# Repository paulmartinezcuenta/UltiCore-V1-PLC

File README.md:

# UltiCore V1 - ESP32-Based Industrial PLC 

UltiCore V1 is a high-reliability, industrial-grade Programmable Logic Controller (PLC) custom-designed around the **ESP32-WROOM-32D** architecture. Engineered for harsh electrical environments, this board features high-density optical isolation, dedicated buffered data buses, and a robust power management system.

---

##  Advanced Hardware Architecture & Engineering

### 1. Dual-Bus Data Architecture & Control Logic
* **Buffered Bus Isolation:** Implements octal three-state buffers (**74HC541TS**) to split control signals into dedicated **Power Data Buses** and **Analog Data Buses**. This topology isolates the MCU pins, maximizes fan-out capability, and prevents EMI crosstalk from high-current switching sections.
* **Industrial Output Stage (8-Channel Relay Matrix):** Features 8 independent mechanical relays driven by robust **2N3904** BJT switching circuits. Each channel is equipped with hardwired pull-down networks for deterministic power-up states and **RR1VWM6STFTR** flyback suppression diodes to clamp inductive back-EMF spikes.

### 2. High-Density Input Conditioning & Galvanic Isolation
* **Optically Isolated Digital Inputs:** 8 industrial-level input channels (`IN0`-`IN7`) isolated via high-density **ILD207T** dual optocouplers, establishing complete galvanic separation between the 24V field domain and the 3.3V logic domain.
* **Hardware Debouncing & Waveshaping:** Optocoupler outputs are routed through **74HC14** Hex Schmitt-Trigger inverters to suppress mechanical switch bounce and electrical noise, delivering sharp, clean square waves to the MCU.

### 3. Industrial Power Supply & Protection Framework
* **High-Efficiency Buck Topology:** Integrates an **LM2576HVS-3.3** switching regulator paired with a **100µH** power inductor and a **B330A** Schottky diode to efficiently step down standard industrial 24VDC rails directly to a stable 3.3V rail.
* **Smart Dual-Power Protection (Anti-USB & 24V Cross-Protection):** Utilizes an **LM358DR** operational amplifier comparator circuit coupled with a **PC817** optocoupler and an **FQD11P06** P-Channel MOSFET. This layout actively prevents reverse-current backfeeding and hardware damage when both the high-voltage field power and USB-C programming interface are active simultaneously.
* **Front-End Overcurrent & Polarity Defense:** Equipped with a standard 5x20mm cartridge fuse assembly and a high-current **5S14** blocking diode for reverse-polarity protection.

### 4. Modern Interface & ESD Compliance
* **USB-C Interface:** Modern USB-C implementation driven by a **CH340C** USB-to-UART bridge with an integrated dual-transistor auto-reset/boot-loader circuit.
* **Transient Voltage Suppression:** High-speed **LESD5D5.0CT1G** TVS diode arrays deployed on critical USB data lines (`D+`/`D-`) for localized ESD clamping.

---

## Repository Structure

```text
├── Hardware/        # KiCad schematic captures, multi-layer layout files, and structural BOM
├── Firmware/        # Modular C/C++ source code and RTOS industrial automation tasks
└── Docs/            # Hardware layout sheets, pinout mapping, and component datasheets

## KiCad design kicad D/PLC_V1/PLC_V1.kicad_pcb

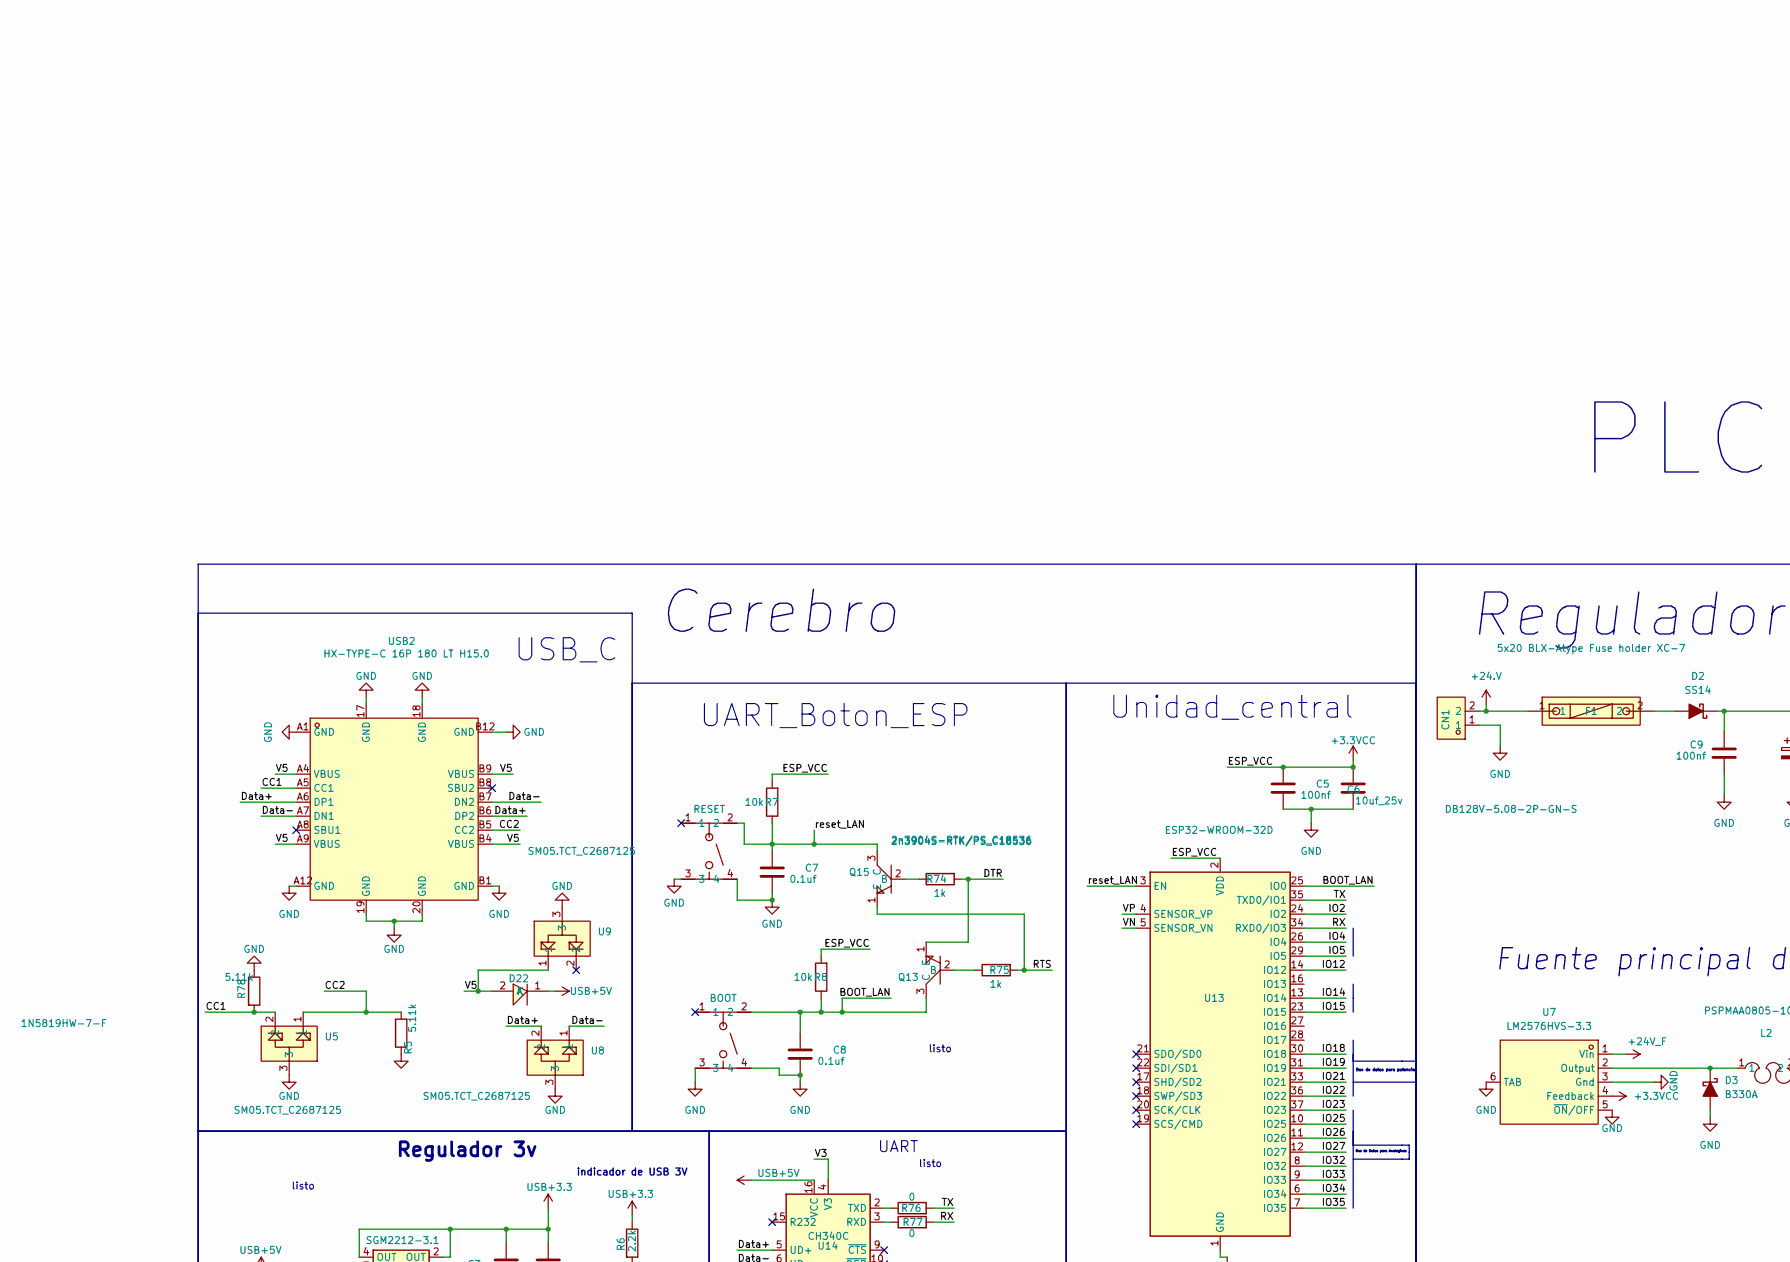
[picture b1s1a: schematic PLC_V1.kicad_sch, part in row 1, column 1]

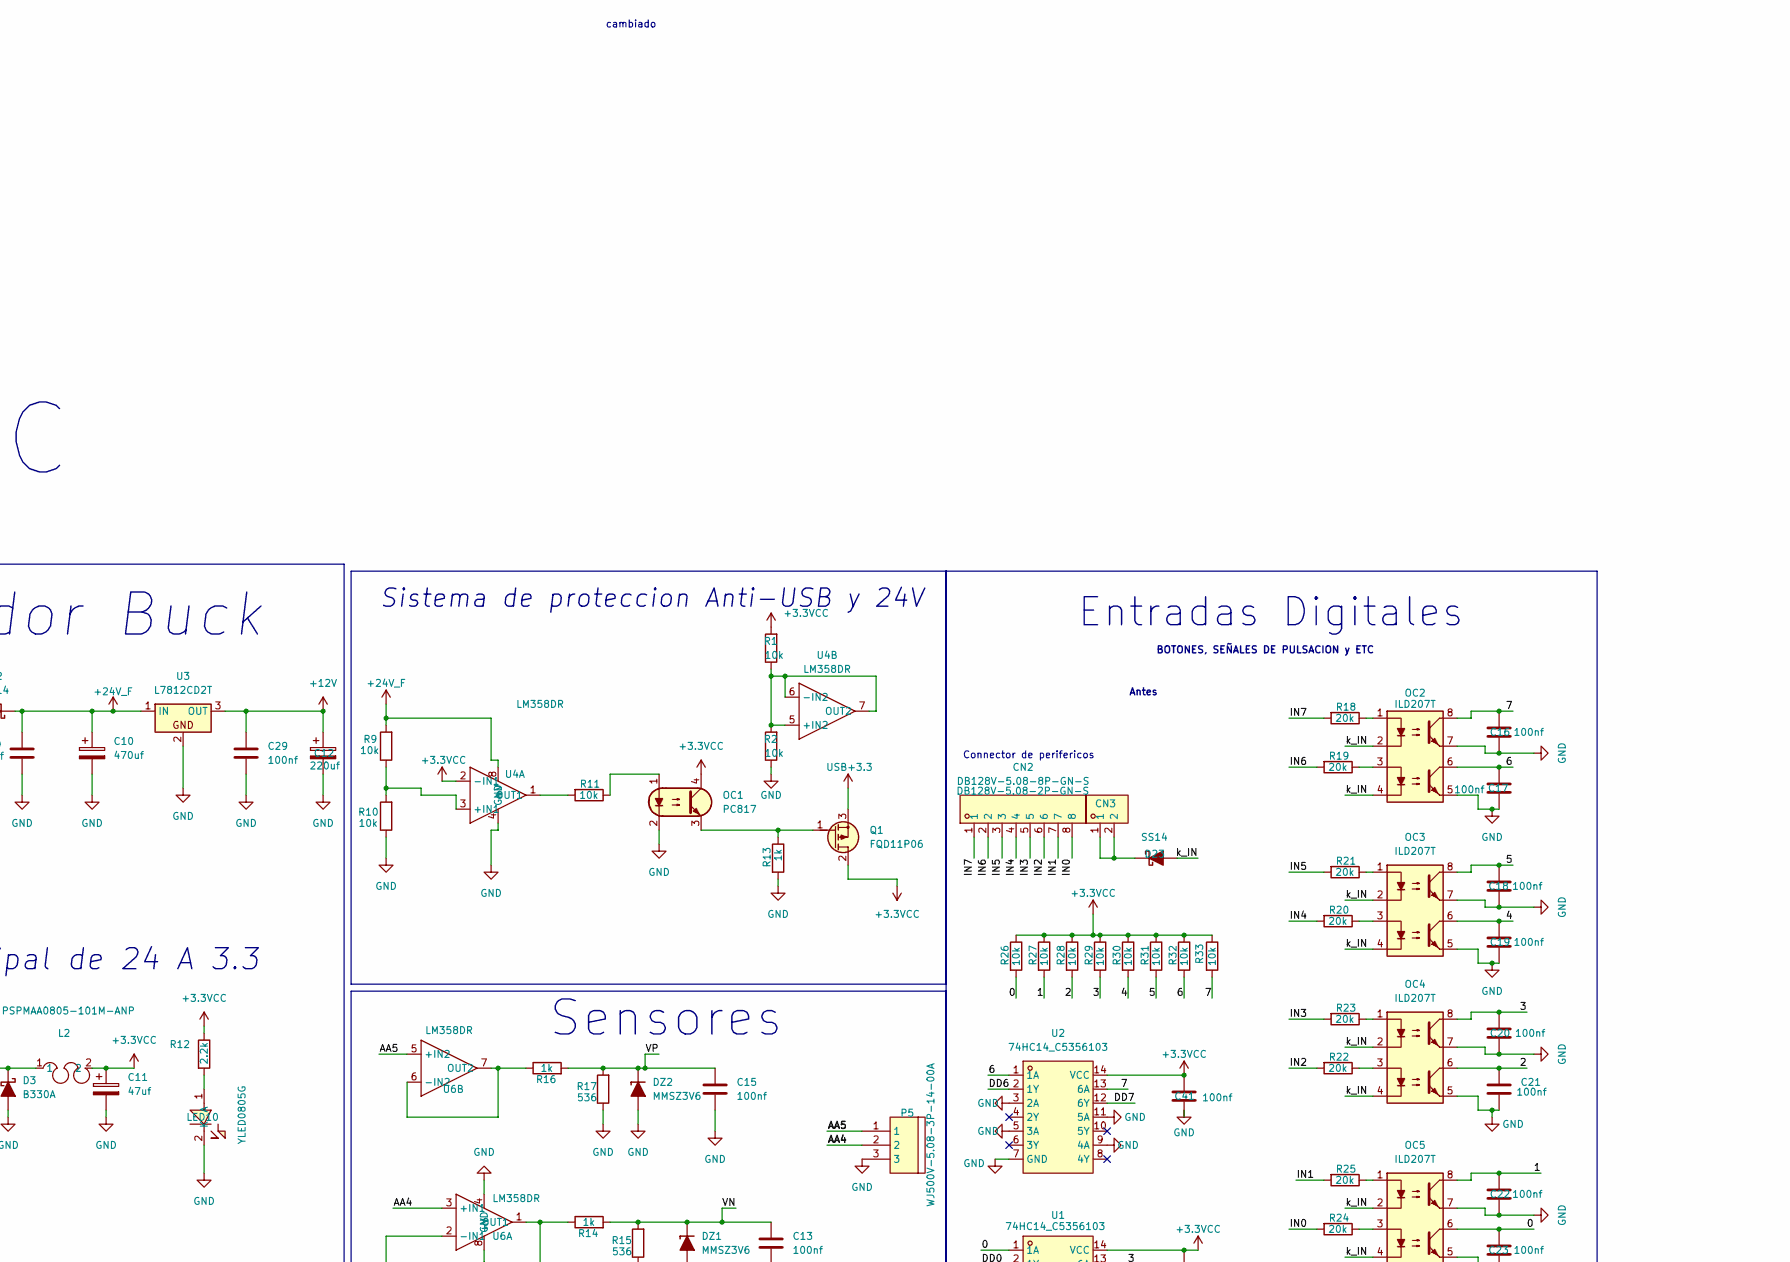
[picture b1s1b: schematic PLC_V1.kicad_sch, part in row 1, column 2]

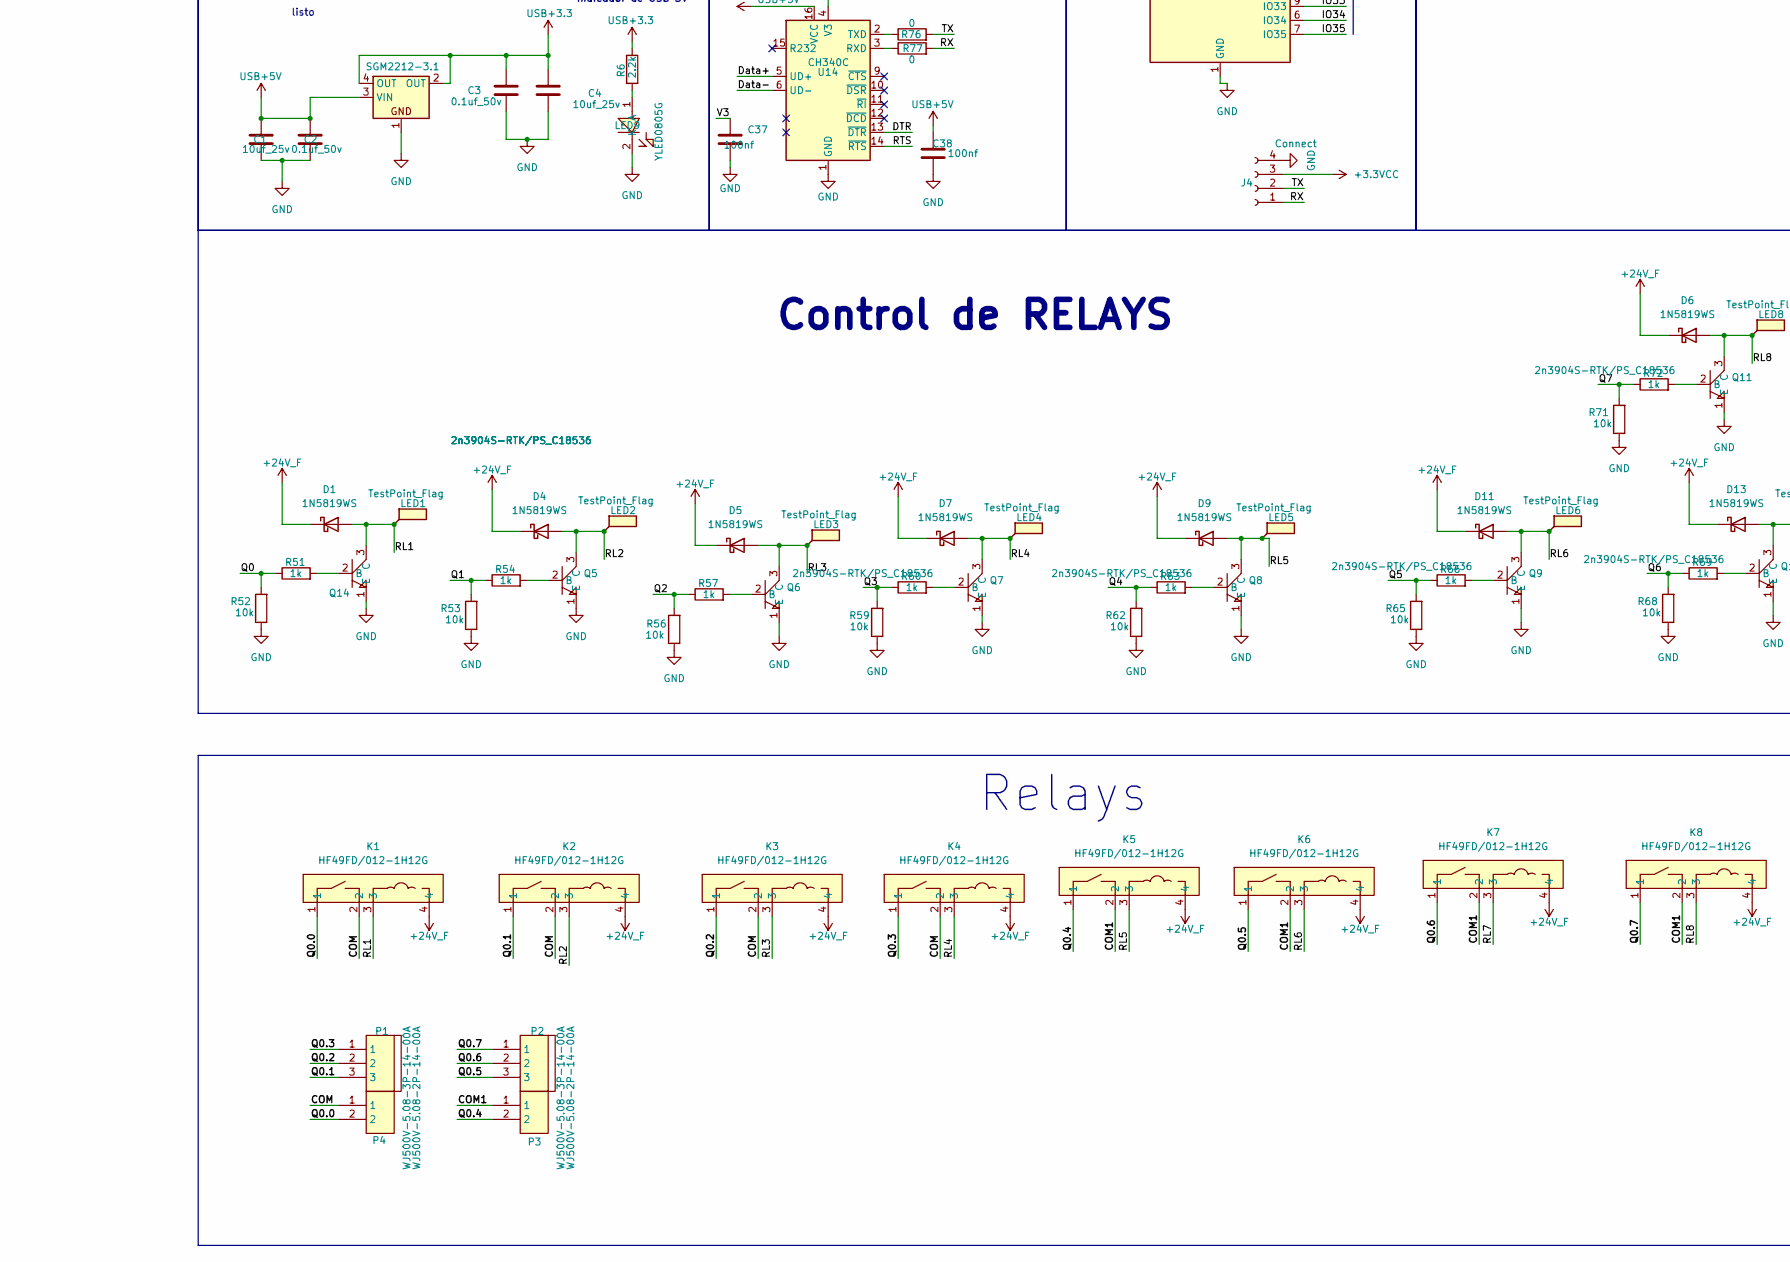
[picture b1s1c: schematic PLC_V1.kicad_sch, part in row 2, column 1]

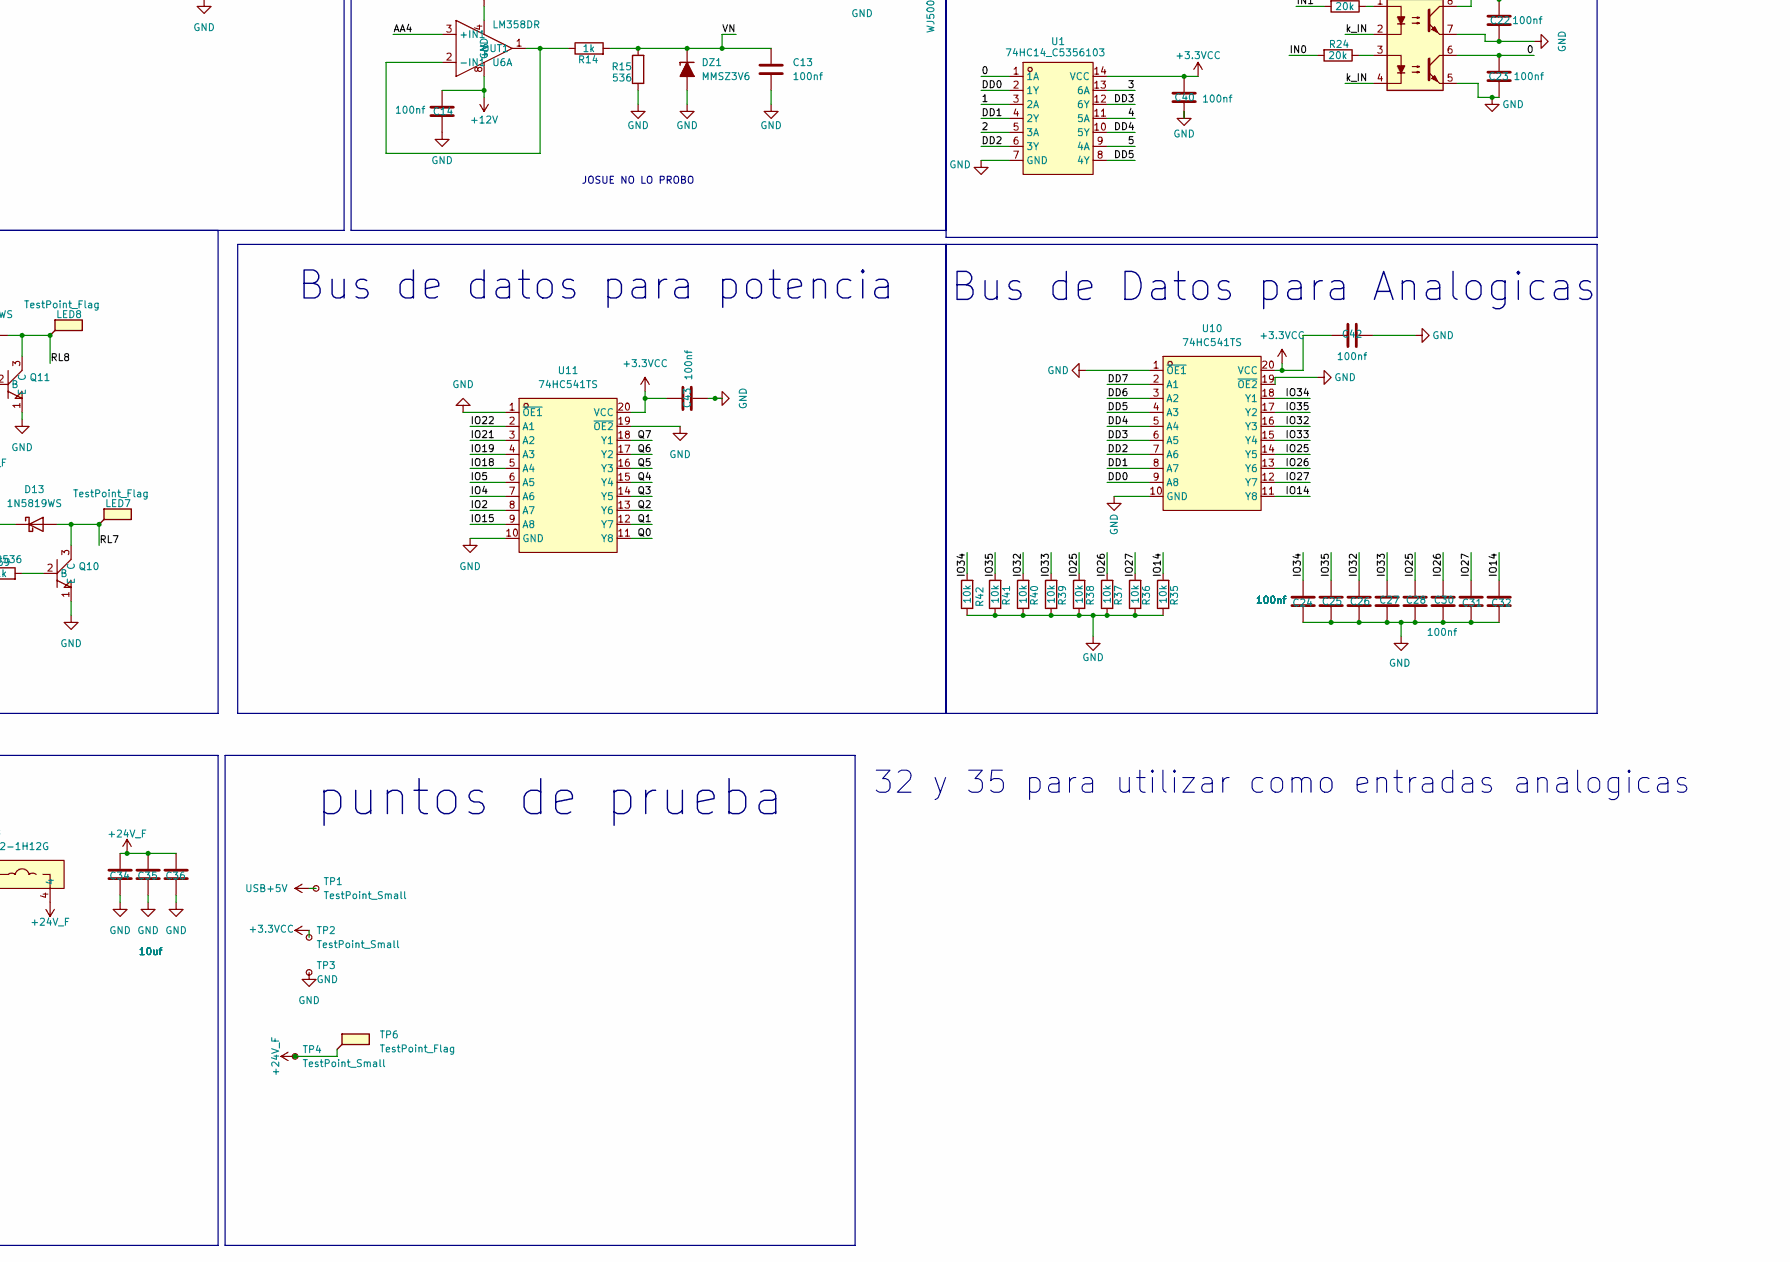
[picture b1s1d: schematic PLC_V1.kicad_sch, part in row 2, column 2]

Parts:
C1, C4, C6: 10uf_25v; C_0805_2012Metric_Pad1.18x1.45mm_HandSolder
C2, C3: 0.1uf_50v; C_0805_2012Metric_Pad1.18x1.45mm_HandSolder
C5, C9, C13, C14, C15, C16, C17, C18, C19, C20, C21, C22, C23, C24, C25, C26, C27, C28, C29, C30, C31, C32, C37, C38, C40, C41, C42, C43: 100nf; C_0805_2012Metric_Pad1.18x1.45mm_HandSolder
C7, C8: 0.1uf; C_0805_2012Metric_Pad1.18x1.45mm_HandSolder
C10: 470uf; C_Elec_10x10.2; LCSC C72518
C11: 47uf; C_Elec_6.3x7.7; LCSC C72523
C12: 220uf; C_Elec_8x10.2
C34, C35, C36: 10uf; C_0805_2012Metric_Pad1.18x1.45mm_HandSolder
CN1, CN3: DB128V-5.08-2P-GN-S; CONN-TH_2P-P5.08_DIBO_DB128V-5.08; LCSC Part C2915639
CN2: DB128V-5.08-8P-GN-S; CONN-TH_8P-P5.08_DB128V-5.08-8P-GN-S; LCSC Part C5143711
D1, D4, D5, D6, D7, D9, D11, D13: 1N5819WS; D_SOD-323
D2, D23: SS14; D_SMA
D3: B330A; D_SMA
D22: 1N5819HW-7-F; SOD-123_L2.7-W1.6-LS3.7-RD; LCSC Part C82544
DZ1, DZ2: MMSZ3V6; D_SOD-123
F1: 5x20 BLX-Atype Fuse holder XC-7; FUSE-TH_L22.6-W9.0; LCSC Part C3131
J4: Connect; PinHeader_1x04_P2.00mm_Vertical
K1, K2, K3, K4, K5, K6, K7, K8: HF49FD/012-1H12G; RELAY-TH_HF49FD-012-1H12G; LCSC Part C340662
L2: PSPMAA0805-101M-ANP; IND-SMD_L8.5-W8.0_PCC-M0854M; LCSC Part C2962892
LED1, LED2, LED3, LED4, LED5, LED6, LED7, LED8: TestPoint_Flag; SolderWirePad_1x01_SMD_1x2mm
LED9, LED10: YLED0805G; LED0805-FD-GREEN; LCSC Part C25170728
OC1: PC817; DIP-4_W7.62mm_SMDSocket_SmallPads
OC2, OC3, OC4, OC5: ILD207T; SO-8_3.9x6.2mm_P1.27mm
P1, P2, P5: WJ500V-5.08-3P-14-00A; CONN-TH_3P-P5.00_WJ500V-5.08-3P; LCSC Part C72334
P3, P4: WJ500V-5.08-2P-14-00A; CONN-TH_2P-P5.00_WJ500V-5.08-2P; LCSC Part C8465
Q1: FQD11P06; TO-252-2
Q5, Q6, Q7, Q8, Q9, Q10, Q11, Q13, Q14, Q15: 2n3904S-RTK/PS_C18536; SOT-23-3_L2.9-W1.3-P1.90-LS2.4-TR; LCSC Part C18536
R1, R2, R7, R8, R9, R10, R11, R26, R27, R28, R29, R30, R31, R32, R33, R35, R36, R37, R38, R39, R40, R41, R42, R52, R53, R56, R59, R62, R65, R68, R71: 10k; R_0805_2012Metric_Pad1.20x1.40mm_HandSolder
R5, R78: 5.11k; R_0805_2012Metric_Pad1.20x1.40mm_HandSolder
R6, R12: 2.2k; R_0805_2012Metric_Pad1.20x1.40mm_HandSolder
R13, R14, R16, R51, R54, R57, R60, R63, R66, R69, R72, R74, R75: 1k; R_0805_2012Metric_Pad1.20x1.40mm_HandSolder
R15, R17: 536; R_0805_2012Metric_Pad1.20x1.40mm_HandSolder
R18, R19, R20, R21, R22, R23, R24, R25: 20k; R_0805_2012Metric_Pad1.20x1.40mm_HandSolder
R76, R77: 0; R_0805_2012Metric_Pad1.20x1.40mm_HandSolder
SGM2212-3.1: SOT-223
SW1: BOOT; SW-SMD_4P-L6.0-W6.0-P4.50-LS8.2; LCSC Part C7528752
SW3: RESET; SW-SMD_4P-L6.0-W6.0-P4.50-LS8.2; LCSC Part C7528752
TP1, TP2, TP4: TestPoint_Small; TestPoint_Pad_2.0x2.0mm
TP3: GND; TestPoint_Pad_2.0x2.0mm
TP6: TestPoint_Flag; SolderWirePad_1x01_SMD_1.5x3mm
U1, U2: 74HC14_C5356103; SOIC-14_L8.7-W3.9-P1.27-LS6.0-BL; LCSC Part C5356103
U3: L7812CD2T; TO-263-2
U4, U6: LM358DR; SOIC-8_L5.0-W4.0-P1.27-LS6.0-BL; LCSC Part C5423
U5, U8, U9: SM05.TCT_C2687125; SOT-23-3_L2.9-W1.3-P1.90-LS2.4; LCSC Part C2687125
U7: LM2576HVS-3.3; PG-TO-263-5_L10.2-W8.7-P1.70-LS14.4-BR; LCSC Part C347436
U10, U11: 74HC541TS; TSSOP-20_L6.5-W4.4-P0.65-LS6.4-BL; LCSC Part C41433435
U13: ESP32-WROOM-32D
U14: CH340C; SOIC-16_3.9x9.9mm_P1.27mm
USB2: HX-TYPE-C 16P 180 LT H15.0; USB-C-SMD_HX-TYPE-C-16P-180-LT-H15.0; LCSC Part C49261573

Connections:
+3.3VCC: C5.1, C6.1, C11.1, C40.2, C41.2, C42.1, C43.2, J4.3, L2.2, OC1.4, Q1.2 (D), R1.2, R7.2, R8.2, R12.1, R26.1, R27.1, R28.1, R29.1, R30.1, R31.1, R32.1, R33.1, TP2.1, U1.14 (VCC), U2.14 (VCC), U4.2 (-IN1), U7.4 (Feedback), U10.20 (VCC), U11.20 (VCC), U13.2 (VDD)
+12V: C12.1, C14.1, C29.1, U3.3 (OUT), U6.8 (+V)
+24.V: CN1.2, F1.1
+24V_F: C9.1, C10.1, C34.1, C35.1, C36.1, D1.1 (K), D2.1 (K), D4.1 (K), D5.1 (K), D6.1 (K), D7.1 (K), D9.1 (K), D11.1 (K), D13.1 (K), K1.4, K2.4, K3.4, K4.4, K5.4, K6.4, K7.4, K8.4, R9.2, TP4.1, TP6.1, U3.1 (IN), U4.8 (+V), U7.1 (Vin)
/0: C23.1, OC5.6, R26.2, U1.1 (1A)
/1: C22.1, OC5.8, R27.2, U1.3 (2A)
/2: C21.1, OC4.6, R28.2, U1.5 (3A)
/3: C20.1, OC4.8, R29.2, U1.13 (6A)
/4: C19.1, OC3.6, R30.2, U1.11 (5A)
/5: C18.1, OC3.8, R31.2, U1.9 (4A)
/6: C17.1, OC2.6, R32.2, U2.1 (1A)
/7: C16.1, OC2.8, R33.2, U2.13 (6A)
/AA4: P5.2, U6.3 (+IN1)
/AA5: P5.1, U6.5 (+IN2)
/BOOT_LAN: C8.1, Q13.3 (C), R8.1, SW1.2, U13.25 (IO0)
/CC1: R78.2, U5.2, USB2.A5 (CC1)
/CC2: R5.2, U5.1, USB2.B5 (CC2)
/COM: K1.2, K2.2, K3.2, K4.2, P4.1
/COM1: K5.2, K6.2, K7.2, K8.2, P3.1
/DD0: U1.2 (1Y), U10.9 (A8)
/DD1: U1.4 (2Y), U10.8 (A7)
/DD2: U1.6 (3Y), U10.7 (A6)
/DD3: U1.12 (6Y), U10.6 (A5)
/DD4: U1.10 (5Y), U10.5 (A4)
/DD5: U1.8 (4Y), U10.4 (A3)
/DD6: U2.2 (1Y), U10.3 (A2)
/DD7: U2.12 (6Y), U10.2 (A1)
/DTR: Q13.1 (E), R74.2, U14.13 (~DTR)
/Data+: U8.2, U14.5 (UD+), USB2.A6 (DP1), USB2.B6 (DP2)
/Data-: U8.1, U14.6 (UD-), USB2.A7 (DN1), USB2.B7 (DN2)
/IN0: CN2.8, R24.2
/IN1: CN2.7, R25.2
/IN2: CN2.6, R22.2
/IN3: CN2.5, R23.2
/IN4: CN2.4, R20.2
/IN5: CN2.3, R21.2
/IN6: CN2.2, R19.2
/IN7: CN2.1, R18.2
/IO2: U11.8 (A7), U13.24 (IO2)
/IO4: U11.7 (A6), U13.26 (IO4)
/IO5: U11.6 (A5), U13.29 (IO5)
/IO12: U13.14 (IO12)
/IO14: C32.1, R35.2, U10.11 (Y8), U13.13 (IO14)
/IO15: U11.9 (A8), U13.23 (IO15)
/IO18: U11.5 (A4), U13.30 (IO18)
/IO19: U11.4 (A3), U13.31 (IO19)
/IO21: U11.3 (A2), U13.33 (IO21)
/IO22: U11.2 (A1), U13.36 (IO22)
/IO23: U13.37 (IO23)
/IO25: C28.1, R38.2, U10.14 (Y5), U13.10 (IO25)
/IO26: C30.1, R37.2, U10.13 (Y6), U13.11 (IO26)
/IO27: C31.1, R36.2, U10.12 (Y7), U13.12 (IO27)
/IO32: C26.1, R40.2, U10.16 (Y3), U13.8 (IO32)
/IO33: C27.1, R39.2, U10.15 (Y4), U13.9 (IO33)
/IO34: C24.1, R42.2, U10.18 (Y1), U13.6 (IO34)
/IO35: C25.1, R41.2, U10.17 (Y2), U13.7 (IO35)
/Q0: R51.1, R52.2, U11.11 (Y8)
/Q0.0: K1.1, P4.2
/Q0.1: K2.1, P1.3
/Q0.2: K3.1, P1.2
/Q0.3: K4.1, P1.1
/Q0.4: K5.1, P3.2
/Q0.5: K6.1, P2.3
/Q0.6: K7.1, P2.2
/Q0.7: K8.1, P2.1
/Q1: R53.2, R54.1, U11.12 (Y7)
/Q2: R56.2, R57.1, U11.13 (Y6)
/Q3: R59.2, R60.1, U11.14 (Y5)
/Q4: R62.2, R63.1, U11.15 (Y4)
/Q5: R65.2, R66.1, U11.16 (Y3)
/Q6: R68.2, R69.1, U11.17 (Y2)
/Q7: R71.2, R72.1, U11.18 (Y1)
/RL1: D1.2 (A), K1.3, LED1.1, Q14.3 (C)
/RL2: D4.2 (A), K2.3, LED2.1, Q5.3 (C)
/RL3: D5.2 (A), K3.3, LED3.1, Q6.3 (C)
/RL4: D7.2 (A), K4.3, LED4.1, Q7.3 (C)
/RL5: D9.2 (A), K5.3, LED5.1, Q8.3 (C)
/RL6: D11.2 (A), K6.3, LED6.1, Q9.3 (C)
/RL7: D13.2 (A), K7.3, LED7.1, Q10.3 (C)
/RL8: D6.2 (A), K8.3, LED8.1, Q11.3 (C)
/RTS: Q15.1 (E), R75.2, U14.14 (~RTS)
/RX: J4.1, R77.2, U13.34 (RXD0/IO3)
/TX: J4.2, R76.2, U13.35 (TXD0/IO1)
/V3: C37.1, U14.4 (V3)
/V5: D22.2 (A), U9.1, USB2.A4 (VBUS), USB2.A9 (VBUS), USB2.B4 (VBUS), USB2.B9 (VBUS)
/VN: C13.1, DZ1.1 (K), R14.2, R15.2, U13.5 (SENSOR_VN)
/VP: C15.1, DZ2.1 (K), R16.2, R17.2, U13.4 (SENSOR_VP)
/k_IN: D23.2 (A), OC2.2, OC2.4, OC3.2, OC3.4, OC4.2, OC4.4, OC5.2, OC5.4
/reset_LAN: C7.1, Q15.3 (C), R7.1, SW3.2, U13.3 (EN)
GND: C1.2, C2.2, C3.2, C4.2, C5.2, C6.2, C7.2, C8.2, C9.2, C10.2, C11.2, C12.2, C13.2, C14.2, C15.2, C16.2, C17.2, C18.2, C19.2, C20.2, C21.2, C22.2, C23.2, C24.2, C25.2, C26.2, C27.2, C28.2, C29.2, C30.2, C31.2, C32.2, C34.2, C35.2, C36.2, C37.2, C38.2, C40.1, C41.1, C42.2, C43.1, CN1.1, D3.2 (A), DZ1.2 (A), DZ2.2 (A), J4.4, LED9.2 (K), LED10.2 (K), OC1.2, OC2.5, OC2.7, OC3.5, OC3.7, OC4.5, OC4.7, OC5.5, OC5.7, P5.3, Q5.1 (E), Q6.1 (E), Q7.1 (E), Q8.1 (E), Q9.1 (E), Q10.1 (E), Q11.1 (E), Q14.1 (E), R2.1, R5.1, R10.1, R13.2, R15.1, R17.1, R35.1, R36.1, R37.1, R38.1, R39.1, R40.1, R41.1, R42.1, R52.1, R53.1, R56.1, R59.1, R62.1, R65.1, R68.1, R71.1, R78.1, SGM2212-3.1.1, SW1.3, SW1.4, SW3.3, SW3.4, TP3.1, U1.7 (GND), U2.3 (2A), U2.5 (3A), U2.7 (GND), U2.9 (4A), U2.11 (5A), U3.2, U4.4 (GND), U5.3, U6.4 (GND), U7.3 (Gnd), U7.5 (~ON/OFF), U7.6 (TAB), U8.3, U9.3, U10.1 (~OE1), U10.10 (GND), U10.19 (~OE2), U11.1 (~OE1), U11.10 (GND), U11.19 (~OE2), U13.1 (GND), U13.15 (GND), U13.38 (GND), U13.39 (GND), U14.1 (GND), USB2.17 (GND), USB2.18 (GND), USB2.19 (GND), USB2.20 (GND), USB2.A1 (GND), USB2.A12 (GND), USB2.B1 (GND), USB2.B12 (GND); also elsewhere on the board
unnamed: D2.2 (A), F1.2
unnamed: D3.1 (K), L2.1, U7.2 (Output)
unnamed: CN3.1, CN3.2, D23.1 (K)
unnamed: LED9.1 (A), R6.2
unnamed: LED10.1 (A), R12.2
unnamed: OC1.1, R11.1
unnamed: OC2.1, R18.1
unnamed: OC2.3, R19.1
unnamed: OC3.1, R21.1
unnamed: OC3.3, R20.1
unnamed: OC4.1, R23.1
unnamed: OC4.3, R22.1
unnamed: OC5.1, R25.1
unnamed: OC5.3, R24.1
unnamed: OC1.3, Q1.1 (G), R13.1
unnamed: Q5.2 (B), R54.2
unnamed: Q6.2 (B), R57.2
unnamed: Q7.2 (B), R60.2
unnamed: Q8.2 (B), R63.2
unnamed: Q9.2 (B), R66.2
unnamed: Q10.2 (B), R69.2
unnamed: Q11.2 (B), R72.2
unnamed: Q13.2 (B), R75.1
unnamed: Q14.2 (B), R51.2
unnamed: Q15.2 (B), R74.1
unnamed: R9.1, R10.2, U4.3 (+IN1)
unnamed: R11.2, U4.1 (OUT1)
unnamed: R1.1, R2.2, U4.5 (+IN2), U4.6 (-IN2), U4.7 (OUT2)
unnamed: R14.1, U6.1 (OUT1), U6.2 (-IN1)
unnamed: R16.1, U6.6 (-IN2), U6.7 (OUT2)
unnamed: R77.1, U14.3 (RXD)
unnamed: R76.1, U14.2 (TXD)
USB+3.3: C3.1, C4.1, Q1.3 (S), R6.1, SGM2212-3.1.2 (OUT), SGM2212-3.1.4 (OUT)
USB+5V: C1.1, C2.1, C38.1, D22.1 (K), SGM2212-3.1.3 (VIN), TP1.1, U14.16 (VCC)

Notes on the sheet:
Regulador Buck
PLC
Relays
USB_C
BOTONES, SEÑALES DE PULSACION y ETC
JOSUE NO LO PROBO
Sistema de proteccion Anti-USB y 24V
listo
UART_Boton_ESP
cambiado
UART
Bus de datos para potencia
Fuente principal de 24 A 3.3
puntos de prueba
Entradas Digitales
Bus de Datos para Analogicas
Cerebro
Control de RELAYS
32 y 35 para utilizar como entradas analogicas
indicador de USB 3V
Connector de perifericos
Unidad_central
Regulador 3v
Antes
Sensores

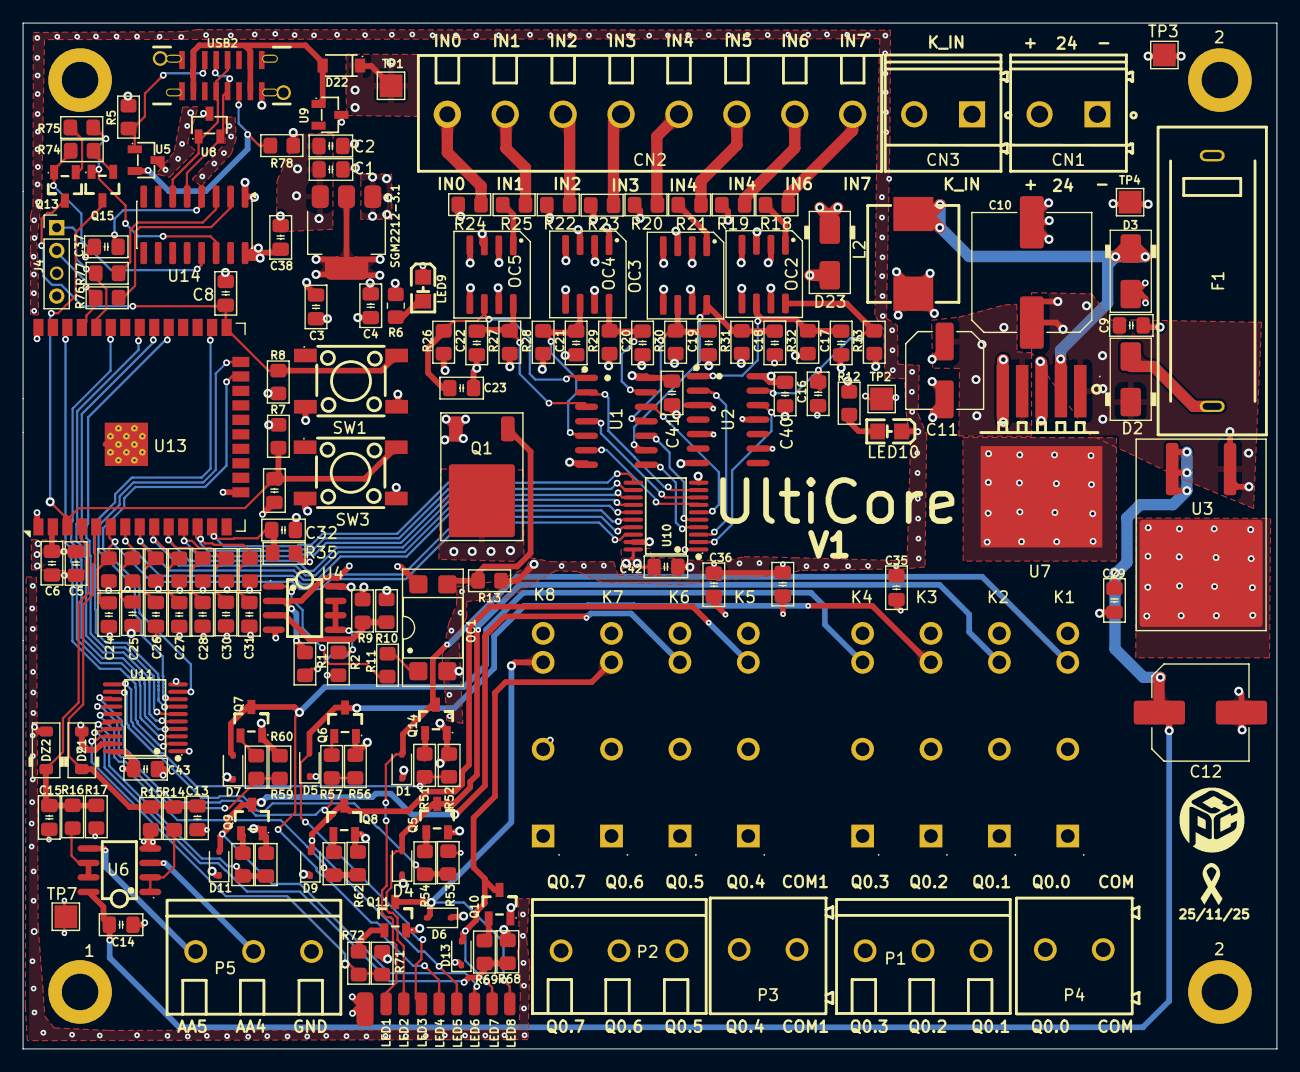
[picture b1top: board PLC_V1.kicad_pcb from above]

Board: 4 copper layers, 110.0 x 90.0 mm, 189 parts (0 on the bottom side), 122 nets.

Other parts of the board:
1, 2, 2#2, 2#3: MountingHole_3.2mm_M3_DIN965_Pad
THECPCENTER: LOGO; IMG1
TP7: GND_U10; TestPoint_Pad_2.0x2.0mm
_: LOGO; LUTO LOGO BIEN

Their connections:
GND: 1.1, 2.1, 2#2.1, 2#3.1, TP7.1; also elsewhere on the board

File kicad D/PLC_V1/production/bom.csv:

Designator,Footprint,Quantity,Value,LCSC Part #
"C1, C4, C6",0805,3,10uf_25v,
C10,C_Elec_10x10.2,1,470uf,C72518
C11,C_Elec_6.3x7.7,1,47uf,C72523
C12,C_Elec_8x10.2,1,220uf,
"C13, C14, C15, C16, C17, C18, C19, C20, C21, C22, C23, C24, C25, C26, C27, C28, C29, C30, C31, C32, C37, C38, C40, C41, C42, C43, C5, C9",0805,28,100nf,
"C2, C3",0805,2,0.1uf_50v,
"C34, C35, C36",0805,3,10uf,
"C7, C8",0805,2,0.1uf,
"CN1, CN3",CONN-TH_2P-P5.08_DIBO_DB128V-5.08,2,DB128V-5.08-2P-GN-S,C2915639
CN2,CONN-TH_8P-P5.08_DB128V-5.08-8P-GN-S,1,DB128V-5.08-8P-GN-S,C5143711
"D1, D11, D13, D4, D5, D6, D7, D9",D_SOD-323,8,1N5819WS,
"D2, D23",D_SMA,2,SS14,
D22,SOD-123_L2.7-W1.6-LS3.7-RD,1,1N5819HW-7-F,C82544
D3,D_SMA,1,B330A,
"DZ1, DZ2",D_SOD-123,2,MMSZ3V6,
F1,FUSE-TH_L22.6-W9.0,1,5x20 BLX-Atype Fuse holder XC-7,C3131
J4,PinHeader_1x04_P2.00mm_Vertical,1,Connect,
"K1, K2, K3, K4, K5, K6, K7, K8",RELAY-TH_HF49FD-012-1H12G,8,HF49FD/012-1H12G,C340662
L2,IND-SMD_L8.5-W8.0_PCC-M0854M,1,PSPMAA0805-101M-ANP,C2962892
"LED1, LED2, LED3, LED4, LED5, LED6, LED7, LED8",SolderWirePad_1x01_SMD_1x2mm,8,TestPoint_Flag,
"LED10, LED9",LED0805-FD-GREEN,2,YLED0805G,C25170728
OC1,DIP-4_W7.62mm_SMDSocket_SmallPads,1,PC817,
"OC2, OC3, OC4, OC5",SO-8_3.9x6.2mm_P1.27mm,4,ILD207T,
"P1, P2, P5",CONN-TH_3P-P5.00_WJ500V-5.08-3P,3,WJ500V-5.08-3P-14-00A,C72334
"P3, P4",CONN-TH_2P-P5.00_WJ500V-5.08-2P,2,WJ500V-5.08-2P-14-00A,C8465
Q1,TO-252-2,1,FQD11P06,
"Q10, Q11, Q13, Q14, Q15, Q5, Q6, Q7, Q8, Q9",SOT-23-3_L2.9-W1.3-P1.90-LS2.4-TR,10,2n3904S-RTK/PS_C18536,C18536
"R1, R10, R11, R2, R26, R27, R28, R29, R30, R31, R32, R33, R35, R36, R37, R38, R39, R40, R41, R42, R52, R53, R56, R59, R62, R65, R68, R7, R71, R8, R9",0805,31,10k,
"R12, R6",0805,2,2.2k,
"R13, R14, R16, R51, R54, R57, R60, R63, R66, R69, R72, R74, R75",0805,13,1k,
"R15, R17",0805,2,536,
"R18, R19, R20, R21, R22, R23, R24, R25",0805,8,20k,
"R5, R78",0805,2,5.11k,
"R76, R77",0805,2,0,
SGM2212-3.1,SOT-223,1,~,
SW1,SW-SMD_4P-L6.0-W6.0-P4.50-LS8.2,1,BOOT,C7528752
SW3,SW-SMD_4P-L6.0-W6.0-P4.50-LS8.2,1,RESET,C7528752
"TP1, TP2, TP4",TestPoint_Pad_2.0x2.0mm,3,TestPoint_Small,
TP3,TestPoint_Pad_2.0x2.0mm,1,GND,
TP6,SolderWirePad_1x01_SMD_1.5x3mm,1,TestPoint_Flag,
TP7,TestPoint_Pad_2.0x2.0mm,1,GND_U10,
"U1, U2",SOIC-14_L8.7-W3.9-P1.27-LS6.0-BL,2,74HC14_C5356103,C5356103
"U10, U11",TSSOP-20_L6.5-W4.4-P0.65-LS6.4-BL,2,74HC541TS,C41433435
U13,ESP32-WROOM-32D,1,ESP32-WROOM-32D,
U14,SOIC-16_3.9x9.9mm_P1.27mm,1,CH340C,
U3,TO-263-2,1,L7812CD2T,
"U4, U6",SOIC-8_L5.0-W4.0-P1.27-LS6.0-BL,2,LM358DR,C5423
"U5, U8, U9",SOT-23-3_L2.9-W1.3-P1.90-LS2.4,3,SM05.TCT_C2687125,C2687125
U7,PG-TO-263-5_L10.2-W8.7-P1.70-LS14.4-BR,1,LM2576HVS-3.3,C347436
USB2,USB-C-SMD_HX-TYPE-C-16P-180-LT-H15.0,1,HX-TYPE-C 16P 180 LT H15.0,C49261573

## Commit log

2026-05-27 Revise README with detailed UltiCore V1 information
    Expanded the README to provide detailed information about the UltiCore V1 PLC, including its hardware architecture, engineering features, and repository structure.
2026-05-27 Add core KiCad schematics and hardware layout files for UltiCore V1
2026-05-27 Add MIT License to the project
2026-06-11 Organización
2026-06-11 Actualización de archivos
